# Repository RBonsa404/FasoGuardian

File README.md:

# FasoGuardian

Système intégré de sécurisation, d'identification et de géolocalisation des enfants au Burkina Faso :
un bracelet connecté, une plateforme serveur et des applications web pour les parents, les agents internes
et toute personne qui trouve un enfant. Projet du Collectif Dedsec (Ouagadougou).

## État d'avancement

Étape 1 « Socle » close le 8 octobre 2026 ; étape 2 en cours (module `identite` : inscription et sessions).
voir [docs/tracabilite.md](docs/tracabilite.md) pour le statut de chacune des 43 user stories.

## Organisation du dépôt

| Dossier | Contenu |
|---|---|
| `backend/` | Serveur Spring Boot 4 en monolithe modulaire : neuf modules métier et un socle technique |
| `frontend/` | Espace de travail Angular 22 : `site`, `parents`, `public-qr`, `console`, bibliothèques `ui` et `api` |
| `simulator/` | Simulateur de bracelets (MQTT en TLS mutuel) |
| `firmware/` | Logiciel embarqué du bracelet : noyau portable et ses essais (port matériel avec le prototype, ADR 0030) |
| `infra/` | Docker Compose, Mosquitto, Nginx, Prometheus, Grafana, Loki |
| `docs/` | ADR, protocoles d'essai, matrice de traçabilité |

## Prérequis

- JDK 21 (la variable `JAVA_HOME` doit pointer dessus), Node.js 24, Docker avec Compose, OpenSSL.
- Maven n'a pas besoin d'être installé : le dépôt fournit `backend/mvnw`.

## Démarrage

**Pour essayer l'application à la main, avec des comptes de démonstration : [docs/tester-en-local.md](docs/tester-en-local.md).**

Préparation, une seule fois : créer le fichier `.env` à partir de `.env.example`, y renseigner les mots de
passe, puis générer les certificats de développement.

```bash
cp .env.example .env
```

```bash
sh infra/generer-certificats-dev.sh
```

Démarrage de tout l'environnement (base, broker, serveur, proxy, observabilité) :

```bash
docker compose --env-file .env -f infra/docker-compose.yml up --build
```

| Service | Adresse |
|---|---|
| API par le proxy (certificat de développement auto-signé) | https://localhost:8443/api/v1/ |
| Broker MQTT (TLS mutuel) | ssl://localhost:8883 |
| Prometheus | http://localhost:9090 |
| Grafana | http://localhost:3000 |

Applications clientes en développement :

```bash
cd frontend && npm ci && npx ng serve parents --proxy-config proxy.dev.json
```

Le fichier `proxy.dev.json` relaie `/api` vers un serveur lancé en local sur le port 8080. Sous le profil
`dev`, les SMS de l'adaptateur bac à sable se lisent sur `GET /api/v1/dev/sms`.

Simulateur de bracelets :

```bash
cd simulator && ../backend/mvnw -f pom.xml package && java -jar target/fasoguardian-simulateur-0.1.0-SNAPSHOT.jar --certificats=../infra/certs --bracelets=FG-DEV-0001,FG-DEV-0002 --intervalle=PT10S --duree=PT1M --cle-plateforme=<clé publique de la plateforme>
```

## Tests

```bash
cd backend && ./mvnw verify
```

```bash
cd frontend && npm test && npm run build && npm run budgets -- parents
```

Les tests d'intégration du serveur démarrent PostgreSQL / PostGIS avec Testcontainers : Docker doit être lancé.

## Architecture

Client-serveur à trois niveaux : applications Angular servies en fichiers statiques, serveur Spring Boot
derrière Nginx, PostgreSQL / PostGIS. Les bracelets communiquent par MQTT en TLS avec authentification
mutuelle, avec repli par SMS signé. Le serveur est découpé en neuf modules (`identite`, `famille`,
`dispositifs`, `telemetrie`, `geolocalisation`, `alertes`, `notifications`, `abonnements`, `audit`) dont les
frontières sont vérifiées à chaque construction.

## Documentation

- Documents de conception FG-DOC-01 à FG-DOC-11 : diffusion restreinte, conservés hors du dépôt
- [Décisions d'architecture](docs/adr/README.md)
- [Matrice de traçabilité](docs/tracabilite.md)
- [Protocoles d'essai](docs/essais/README.md)
- [Guide de contribution](CONTRIBUTING.md)

## Données personnelles

Le projet traite des données d'identité, de santé et de géolocalisation de mineurs. Les données de
démonstration sont fictives. La mise en production avec des données réelles est subordonnée à l'analyse
d'impact (AIPD), à la désignation d'un délégué à la protection des données et aux formalités auprès de la CIL.

## Licence

[MIT](LICENSE) — © 2026 Collectif Dedsec.

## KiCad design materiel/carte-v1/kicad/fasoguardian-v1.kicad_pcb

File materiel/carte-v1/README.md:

# Carte électronique V1 du bracelet

Circuit imprimé de l'étape V1 « Premier circuit » de FG-DOC-08 (§ 12) : 6 couches, 1,2 mm, ENIG, 41 × 36 mm, assemblage
double face. Les décisions et les écarts au document de conception sont dans [CAHIER.md](CAHIER.md) et
[l'ADR 0042](../../docs/adr/0042-carte-v1-du-bracelet.md).

## Une seule source de vérité

Tout part de [conception/carte.py](conception/carte.py). Pour chaque composant, il décrit :
- son symbole et son empreinte ;
- sa valeur, sa référence fabricant et LCSC ;
- sa face d'assemblage ;
- la liaison de chacune de ses broches, par numéro contrôlé sur la fiche du fabricant.

Le schéma, le circuit imprimé et le dossier de fabrication sont générés à partir de ce fichier. On ne les retouche
pas à la main : on corrige `carte.py`, puis on rejoue la chaîne.

## Chaîne de réalisation et points de contrôle

| Étape | Commande | Contrôle |
|---|---|---|
| 1. Netlist | `python conception/verifier.py` | Règles du bracelet : broches du tableau 8 et fonctions alternatives, domaines 1,8 / 3,3 V, PWRKEY et RESET, adresses I²C, réservoir ≥ 300 µF, ≤ 100 µF sur SYS, découplage de chaque rail, hauteur en face inférieure |
| 2. Schéma | `python conception/generer_schema.py` puis `kicad-cli sch erc` | ERC sans erreur ni avertissement, broches typées d'après les fiches (`typer_broches.py`) |
| 3. Placement | `KICAD_PY conception/generer_carte.py` | DRC avec parité schéma ↔ carte ; chemin du courant fort du modem pré-routé et verrouillé |
| 4. Routage | `KICAD_PY conception/relier_plans.py avant`, `KICAD_PY conception/router.py 60` (Freerouting), `KICAD_PY conception/relier_plans.py`, `KICAD_PY conception/finir.py 14` (puis `finir.py fenetre 1.0` si un quartier reste saturé), `KICAD_PY conception/elargir.py` | DRC sans erreur ni avertissement, aucune liaison manquante ; `KICAD_PY conception/controler_carte.py` : lignes RF ≤ 20 mm et sans via, chemin du modem ≤ 30 mΩ de cuivre (`resistance.py`), rail 1V8 ≥ 0,25 mm, plan VBAT d'un seul tenant ; revue `KICAD_PY conception/auditer.py` (découplage au pied des broches, masse sous les lignes RF et coutures, îlots des plans, vias des pastilles thermiques, distance au bord) |
| 5. Fabrication | `python outils/rotations_jlc.py` (après tout changement d'empreinte), `KICAD_PY conception/modeles_3d.py`, puis `python conception/fabriquer.py` | Empreintes identiques à celles de LCSC en orientation et en centre (sinon `fabriquer.py` refuse le placement) ; modèles 3D recopiés de la bibliothèque, hauteur de la face inférieure ≤ 1,35 mm d'après les fiches des fabricants ; Gerber, perçage, netlist, nomenclature (une ligne par référence LCSC) et placement à la convention JLCPCB (rotation de la face inférieure : 180° − angle KiCad), PDF, STEP, rendus ; options de commande dans `fabrication/COMMANDE.md` |
| 6. Commande | `python outils/stock_jlc.py 5` | Stock et coût des pièces pour 5 cartes |
| 7. Guide | `KICAD_PY guide/plans.py`, puis `node guide/imprimer.mjs` | Plans de câblage et de mesure, guide PDF de commande et de mise en service |

`KICAD_PY` est l'interpréteur Python de KiCad :
`C:\Users\rachi\AppData\Local\Programs\KiCad\10.0\bin\python.exe`.
Outils utilisés :
- KiCad 10.0.6 ;
- Freerouting 2.5.0 (Java 25, appelé par son chemin ; le projet garde le JDK 21) ;
- `easyeda2kicad` pour importer les pièces LCSC dans `bibliotheque/`. Chaque pièce importée est contrôlée contre la
  fiche de son fabricant : l'empreinte du module A7670E l'a été plot par plot contre la table SIMCom.

Deux revues indépendantes ont été menées, l'une sur le cahier, l'autre sur le schéma. Leurs conclusions sont reprises
dans `CAHIER.md` et dans l'ADR 0042.

## Contenu

- `conception/` : netlist de référence, générateurs, contrôles.
- `bibliotheque/` : symboles, empreintes et modèles 3D des pièces LCSC.
- `kicad/` : projet KiCad généré (schéma, carte, rapports ERC et DRC).
- `fabrication/` : dossier à envoyer au façonnier.
- `guide/` : guide de commande et de mise en service (`guide-commande-et-mise-en-service.pdf`) et ses sources.
- `outils/` : recherche des références chez JLCPCB, stock et coût, comparaison des empreintes avec LCSC, calcul
  d'impédance.

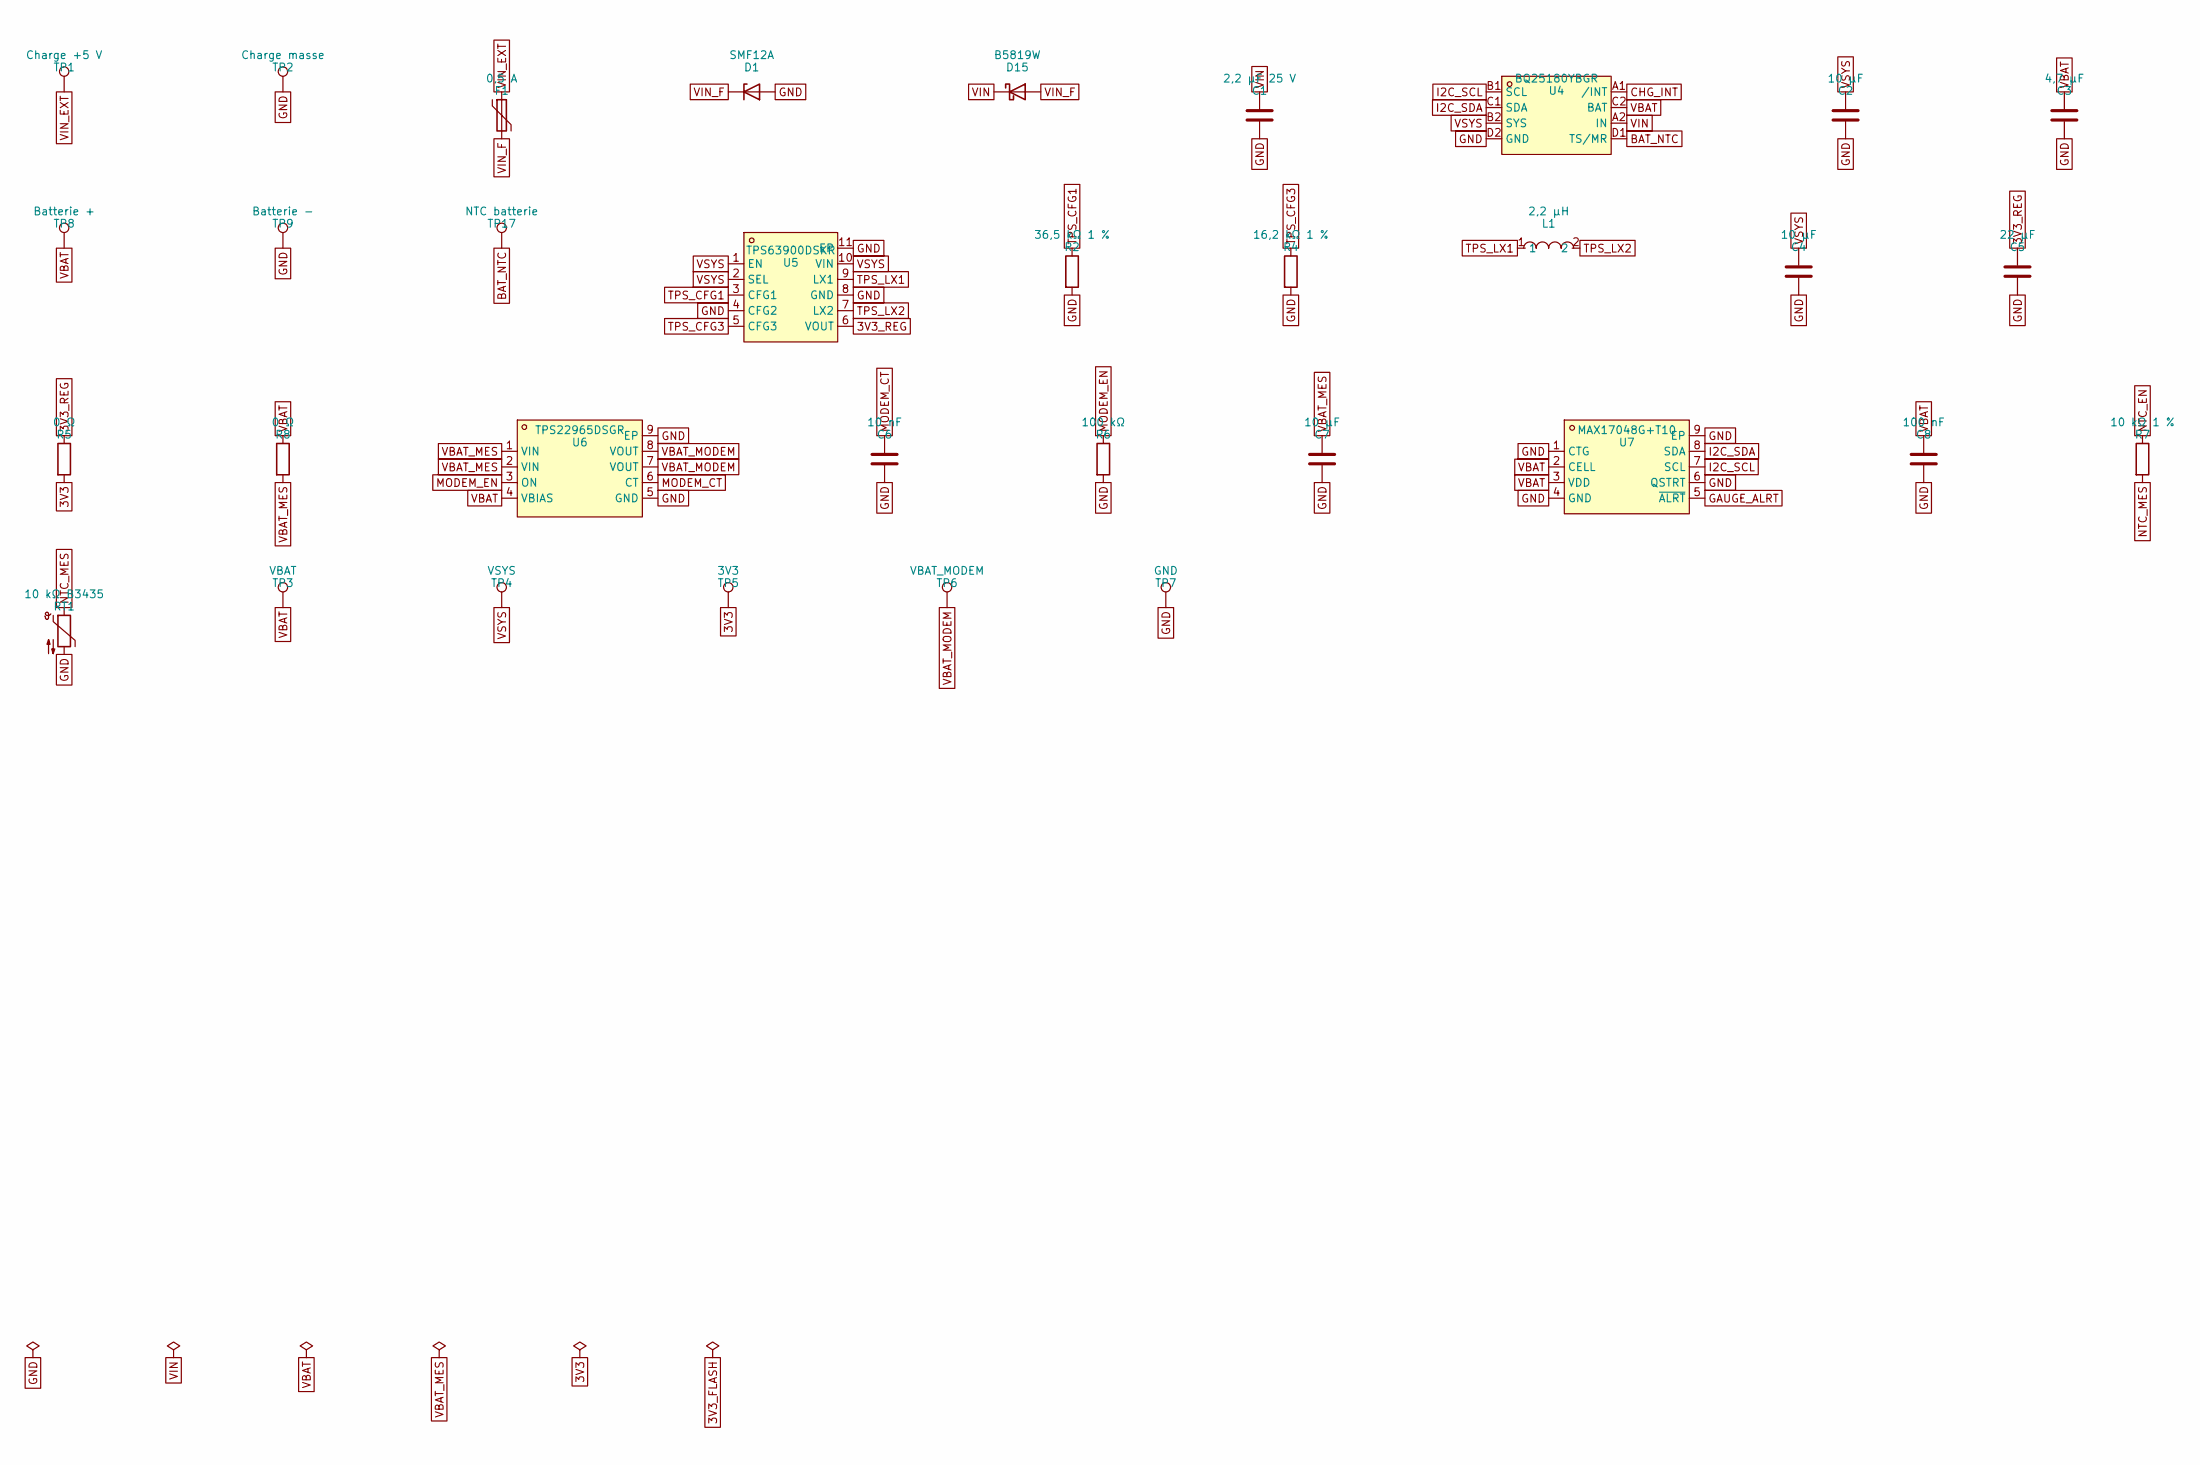
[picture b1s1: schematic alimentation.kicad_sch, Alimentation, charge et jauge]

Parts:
C1: 2,2 µF 25 V; C_0603_1608Metric; LCSC C57895
C2, C4, C7: 10 µF; C_0603_1608Metric; LCSC C19702
C3: 4,7 µF; C_0402_1005Metric; LCSC C23733
C5: 22 µF; C_0603_1608Metric; LCSC C59461
C6: 10 nF; C_0402_1005Metric; LCSC C15195
C8: 100 nF; C_0402_1005Metric; LCSC C1525
D1: SMF12A; D_SOD-123F; LCSC C123800
D15: B5819W; D_SOD-123; LCSC C8598
F1: 0,5 A; Fuse_0603_1608Metric; LCSC C207015
L1: 2,2 µH; L1008; LCSC C576403
R2: 36,5 kΩ 1 %; R_0402_1005Metric; LCSC C25887
R4: 16,2 kΩ 1 %; R_0402_1005Metric; LCSC C226806
R5: 0 Ω; R_0603_1608Metric; LCSC C21189
R6: 100 kΩ; R_0402_1005Metric; LCSC C25741
R7: 10 kΩ 1 %; R_0402_1005Metric; LCSC C25744
R8: 0 Ω; R_1206_3216Metric; LCSC C17888
RT1: 10 kΩ B3435; R_0402_1005Metric; LCSC C77131
TP1: Charge +5 V; TestPoint_Pad_2.5x2.5mm
TP2: Charge masse; TestPoint_Pad_2.5x2.5mm
TP3: VBAT; TestPoint_Pad_D1.0mm
TP4: VSYS; TestPoint_Pad_D1.0mm
TP5: 3V3; TestPoint_Pad_D1.0mm
TP6: VBAT_MODEM; TestPoint_Pad_D1.0mm
TP7: GND; TestPoint_Pad_D1.0mm
TP8: Batterie +; TestPoint_Pad_2.5x2.5mm
TP9: Batterie −; TestPoint_Pad_2.5x2.5mm
TP17: NTC batterie; TestPoint_Pad_1.5x1.5mm
U4: BQ25180YBGR; DSBGA-8_L1.6-W0.9-R2-C4-P0.40-BL; LCSC C3682423
U5: TPS63900DSKR; WSON-10_L2.5-W2.5-W0.50-TL-EP; LCSC C1518762
U6: TPS22965DSGR; UDFN-8_L2.0-W2.0-P0.50-TL-EP; LCSC C122837
U7: MAX17048G+T10; TDFN-8_L2.0-W2.0-P0.50-BL-EP1.2; LCSC C2682616

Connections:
3V3: R5.2, TP5.1; also elsewhere on the board
3V3_REG: C5.1, R5.1, U5.6 (VOUT)
BAT_NTC: TP17.1, U4.D1 (TS/MR)
CHG_INT: U4.A1 (/INT); also elsewhere on the board
GAUGE_ALRT: U7.5 (~ALRT); also elsewhere on the board
GND: C1.2, C2.2, C3.2, C4.2, C5.2, C6.2, C7.2, C8.2, D1.2 (A), R2.2, R4.2, R6.2, RT1.2, TP2.1, TP7.1, TP9.1, U4.D2 (GND), U5.4 (CFG2), U5.8 (GND), U5.11 (EP), U6.5 (GND), U6.9 (EP), U7.1 (CTG), U7.4 (GND), U7.6 (QSTRT), U7.9 (EP); also elsewhere on the board
I2C_SCL: U4.B1 (SCL), U7.7 (SCL); also elsewhere on the board
I2C_SDA: U4.C1 (SDA), U7.8 (SDA); also elsewhere on the board
MODEM_CT: C6.1, U6.6 (CT)
MODEM_EN: R6.1, U6.3 (ON); also elsewhere on the board
NTC_EN: R7.1; also elsewhere on the board
NTC_MES: R7.2, RT1.1; also elsewhere on the board
TPS_CFG1: R2.1, U5.3 (CFG1)
TPS_CFG3: R4.1, U5.5 (CFG3)
TPS_LX1: L1.1, U5.9 (LX1)
TPS_LX2: L1.2, U5.7 (LX2)
VBAT: C3.1, C8.1, R8.1, TP3.1, TP8.1, U4.C2 (BAT), U6.4 (VBIAS), U7.2 (CELL), U7.3 (VDD)
VBAT_MES: C7.1, R8.2, U6.1 (VIN), U6.2 (VIN)
VBAT_MODEM: TP6.1, U6.7 (VOUT), U6.8 (VOUT); also elsewhere on the board
VIN: C1.1, D15.1 (K), U4.A2 (IN)
VIN_EXT: F1.1, TP1.1
VIN_F: D1.1 (K), D15.2 (A), F1.2
VSYS: C2.1, C4.1, TP4.1, U4.B2 (SYS), U5.1 (EN), U5.2 (SEL), U5.10 (VIN); also elsewhere on the board

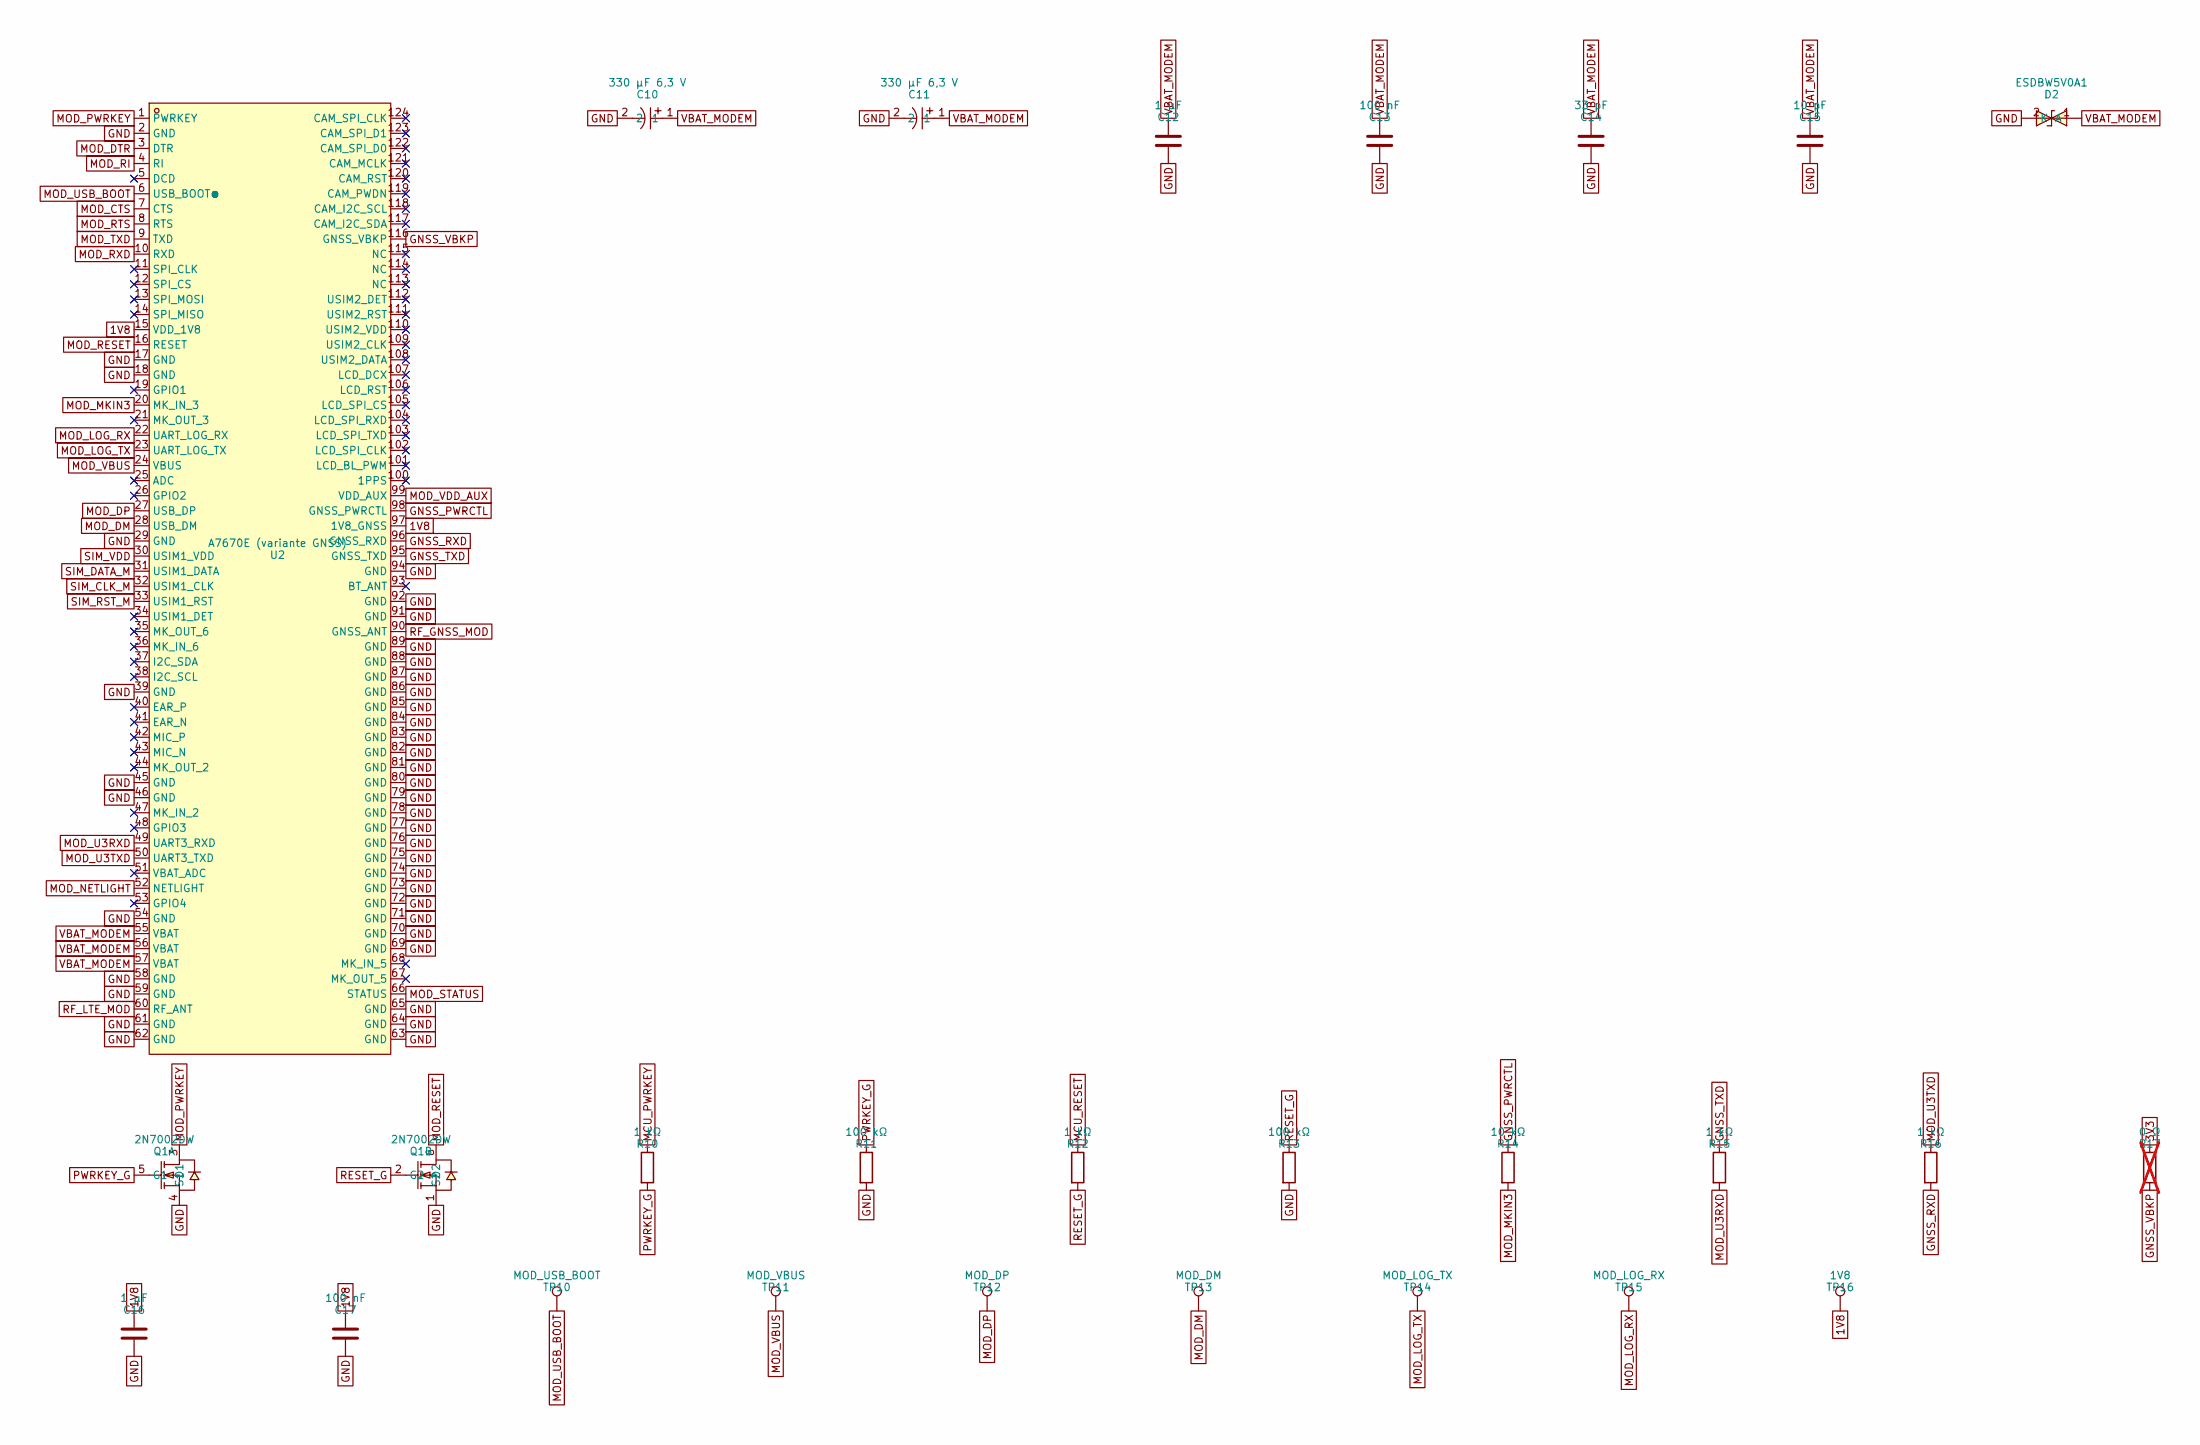
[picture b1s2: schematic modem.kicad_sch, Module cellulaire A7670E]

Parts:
C10, C11: 330 µF 6,3 V; CAP-SMD_L3.5-W2.8-R-RD; LCSC C696806
C12, C16: 1 µF; C_0402_1005Metric; LCSC C52923
C13, C17: 100 nF; C_0402_1005Metric; LCSC C1525
C14: 33 pF; C_0402_1005Metric; LCSC C1562
C15: 10 pF; C_0402_1005Metric; LCSC C32949
D2: ESDBW5V0A1; X1-DFN1006-2_L1.0-W0.6-P0.65-BI; LCSC C5173252
Q1: 2N7002DW; SOT-363_L2.0-W1.3-P0.65-LS2.1-TL; LCSC C83571
R10, R12, R15, R16: 1 kΩ; R_0402_1005Metric; LCSC C11702
R11, R13: 100 kΩ; R_0402_1005Metric; LCSC C25741
R14: 10 kΩ; R_0402_1005Metric; LCSC C25744
R17: 0 Ω; R_0402_1005Metric; LCSC C17168; not fitted
TP10: MOD_USB_BOOT; TestPoint_Pad_D1.0mm
TP11: MOD_VBUS; TestPoint_Pad_D1.0mm
TP12: MOD_DP; TestPoint_Pad_D1.0mm
TP13: MOD_DM; TestPoint_Pad_D1.0mm
TP14: MOD_LOG_TX; TestPoint_Pad_D1.0mm
TP15: MOD_LOG_RX; TestPoint_Pad_D1.0mm
TP16: 1V8; TestPoint_Pad_D1.0mm
U2: A7670E (variante GNSS); LGA-124_L24.0-W24.0-P1.0-A7670C-LASS; LCSC C7435296

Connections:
1V8: C16.1, C17.1, TP16.1, U2.15 (VDD_1V8), U2.97 (1V8_GNSS); also elsewhere on the board
3V3: R17.1; also elsewhere on the board
GND: C10.2, C11.2, C12.2, C13.2, C14.2, C15.2, C16.2, C17.2, D2.2 (A), Q1.1 (S2), Q1.4 (S1), R11.2, R13.2, U2.2 (GND), U2.17 (GND), U2.18 (GND), U2.29 (GND), U2.39 (GND), U2.45 (GND), U2.46 (GND), U2.54 (GND), U2.58 (GND), U2.59 (GND), U2.61 (GND), U2.62 (GND), U2.63 (GND), U2.64 (GND), U2.65 (GND), U2.69 (GND), U2.70 (GND), U2.71 (GND), U2.72 (GND), U2.73 (GND), U2.74 (GND), U2.75 (GND), U2.76 (GND), U2.77 (GND), U2.78 (GND), U2.79 (GND), U2.80 (GND), U2.81 (GND), U2.82 (GND), U2.83 (GND), U2.84 (GND), U2.85 (GND), U2.86 (GND), U2.87 (GND), U2.88 (GND), U2.89 (GND), U2.91 (GND), U2.92 (GND), U2.94 (GND); also elsewhere on the board
GNSS_PWRCTL: R14.1, U2.98 (GNSS_PWRCTL)
GNSS_RXD: R16.2, U2.96 (GNSS_RXD)
GNSS_TXD: R15.1, U2.95 (GNSS_TXD)
GNSS_VBKP: R17.2, U2.116 (GNSS_VBKP)
MCU_PWRKEY: R10.1; also elsewhere on the board
MCU_RESET: R12.1; also elsewhere on the board
MOD_CTS: U2.7 (CTS); also elsewhere on the board
MOD_DM: TP13.1, U2.28 (USB_DM)
MOD_DP: TP12.1, U2.27 (USB_DP)
MOD_DTR: U2.3 (DTR); also elsewhere on the board
MOD_LOG_RX: TP15.1, U2.22 (UART_LOG_RX)
MOD_LOG_TX: TP14.1, U2.23 (UART_LOG_TX)
MOD_MKIN3: R14.2, U2.20 (MK_IN_3)
MOD_NETLIGHT: U2.52 (NETLIGHT); also elsewhere on the board
MOD_PWRKEY: Q1.3 (D1), U2.1 (PWRKEY)
MOD_RESET: Q1.6 (D2), U2.16 (RESET)
MOD_RI: U2.4 (RI); also elsewhere on the board
MOD_RTS: U2.8 (RTS); also elsewhere on the board
MOD_RXD: U2.10 (RXD); also elsewhere on the board
MOD_STATUS: U2.66 (STATUS); also elsewhere on the board
MOD_TXD: U2.9 (TXD); also elsewhere on the board
MOD_U3RXD: R15.2, U2.49 (UART3_RXD)
MOD_U3TXD: R16.1, U2.50 (UART3_TXD)
MOD_USB_BOOT: TP10.1, U2.6 (USB_BOOT●)
MOD_VBUS: TP11.1, U2.24 (VBUS)
MOD_VDD_AUX: U2.99 (VDD_AUX); also elsewhere on the board
PWRKEY_G: Q1.5 (G1), R10.2, R11.1
RESET_G: Q1.2 (G2), R12.2, R13.1
RF_GNSS_MOD: U2.90 (GNSS_ANT); also elsewhere on the board
RF_LTE_MOD: U2.60 (RF_ANT); also elsewhere on the board
SIM_CLK_M: U2.32 (USIM1_CLK); also elsewhere on the board
SIM_DATA_M: U2.31 (USIM1_DATA); also elsewhere on the board
SIM_RST_M: U2.33 (USIM1_RST); also elsewhere on the board
SIM_VDD: U2.30 (USIM1_VDD); also elsewhere on the board
VBAT_MODEM: C10.1, C11.1, C12.1, C13.1, C14.1, C15.1, D2.1 (K), U2.55 (VBAT), U2.56 (VBAT), U2.57 (VBAT); also elsewhere on the board

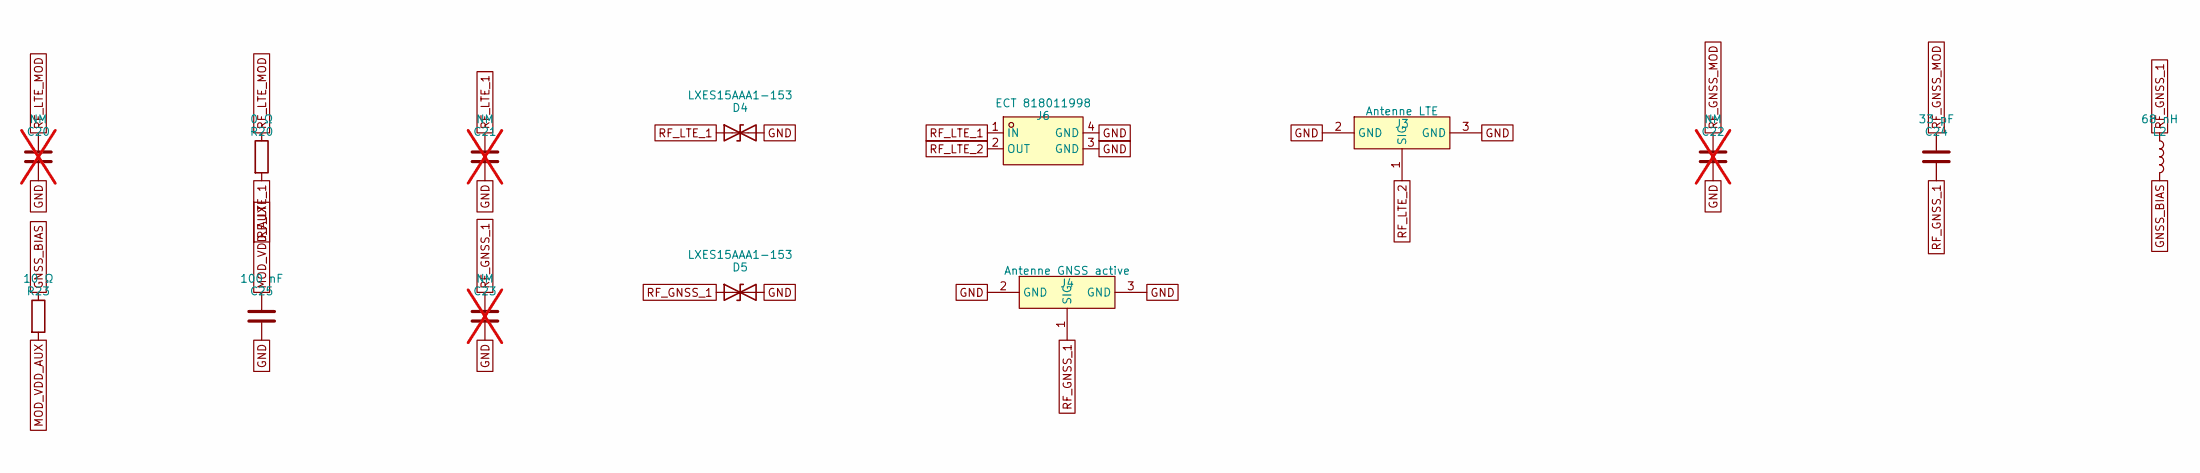
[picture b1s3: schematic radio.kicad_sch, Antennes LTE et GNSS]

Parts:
C20, C21, C22, C23: NM; C_0402_1005Metric; not fitted
C24: 33 pF; C_0402_1005Metric; LCSC C1562
C25: 100 nF; C_0402_1005Metric; LCSC C1525
D4, D5: LXES15AAA1-153; D_0402_1005Metric; LCSC C5210978
J3: Antenne LTE; RF-SMD_FRF05002-JSS103M; LCSC C88374
J4: Antenne GNSS active; RF-SMD_FRF05002-JSS103M; LCSC C88374
J6: ECT 818011998; IPEX-SMD_ECT818011998; LCSC C437250
L2: 68 nH; L_0402_1005Metric; LCSC C108965
R20: 0 Ω; R_0402_1005Metric; LCSC C17168
R23: 10 Ω; R_0402_1005Metric; LCSC C25077

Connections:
GND: C20.2, C21.2, C22.2, C23.2, C25.2, D4.2 (A2), D5.2 (A2), J3.2 (GND), J3.3 (GND), J4.2 (GND), J4.3 (GND), J6.3 (GND), J6.4 (GND); also elsewhere on the board
GNSS_BIAS: L2.2, R23.1
MOD_VDD_AUX: C25.1, R23.2; also elsewhere on the board
RF_GNSS_1: C23.1, C24.2, D5.1 (A1), J4.1 (SIG), L2.1
RF_GNSS_MOD: C22.1, C24.1; also elsewhere on the board
RF_LTE_1: C21.1, D4.1 (A1), J6.1 (IN), R20.2
RF_LTE_2: J3.1 (SIG), J6.2 (OUT)
RF_LTE_MOD: C20.1, R20.1; also elsewhere on the board

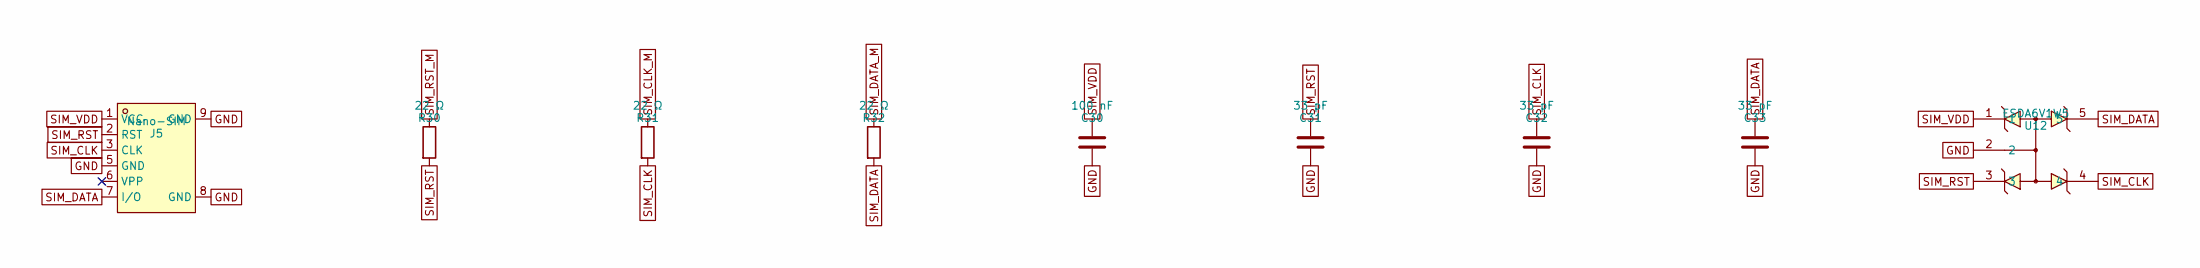
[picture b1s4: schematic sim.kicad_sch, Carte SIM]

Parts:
C30: 100 nF; C_0402_1005Metric; LCSC C1525
C31, C32, C33: 33 pF; C_0402_1005Metric; LCSC C1562
J5: Nano-SIM; SIM-SMD_NANO-SIM-TL6P-H1.35; LCSC C7529385
R30, R31, R32: 22 Ω; R_0402_1005Metric; LCSC C25092
U12: ESDA6V1W5; SC-70-5_L2.1-W1.3-P0.65-LS2.1-BR; LCSC C48677

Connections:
GND: C30.2, C31.2, C32.2, C33.2, J5.5 (GND), J5.8 (GND), J5.9 (GND), U12.2; also elsewhere on the board
SIM_CLK: C32.1, J5.3 (CLK), R31.2, U12.4
SIM_CLK_M: R31.1; also elsewhere on the board
SIM_DATA: C33.1, J5.7 (I/O), R32.2, U12.5
SIM_DATA_M: R32.1; also elsewhere on the board
SIM_RST: C31.1, J5.2 (RST), R30.2, U12.3
SIM_RST_M: R30.1; also elsewhere on the board
SIM_VDD: C30.1, J5.1 (VCC), U12.1; also elsewhere on the board

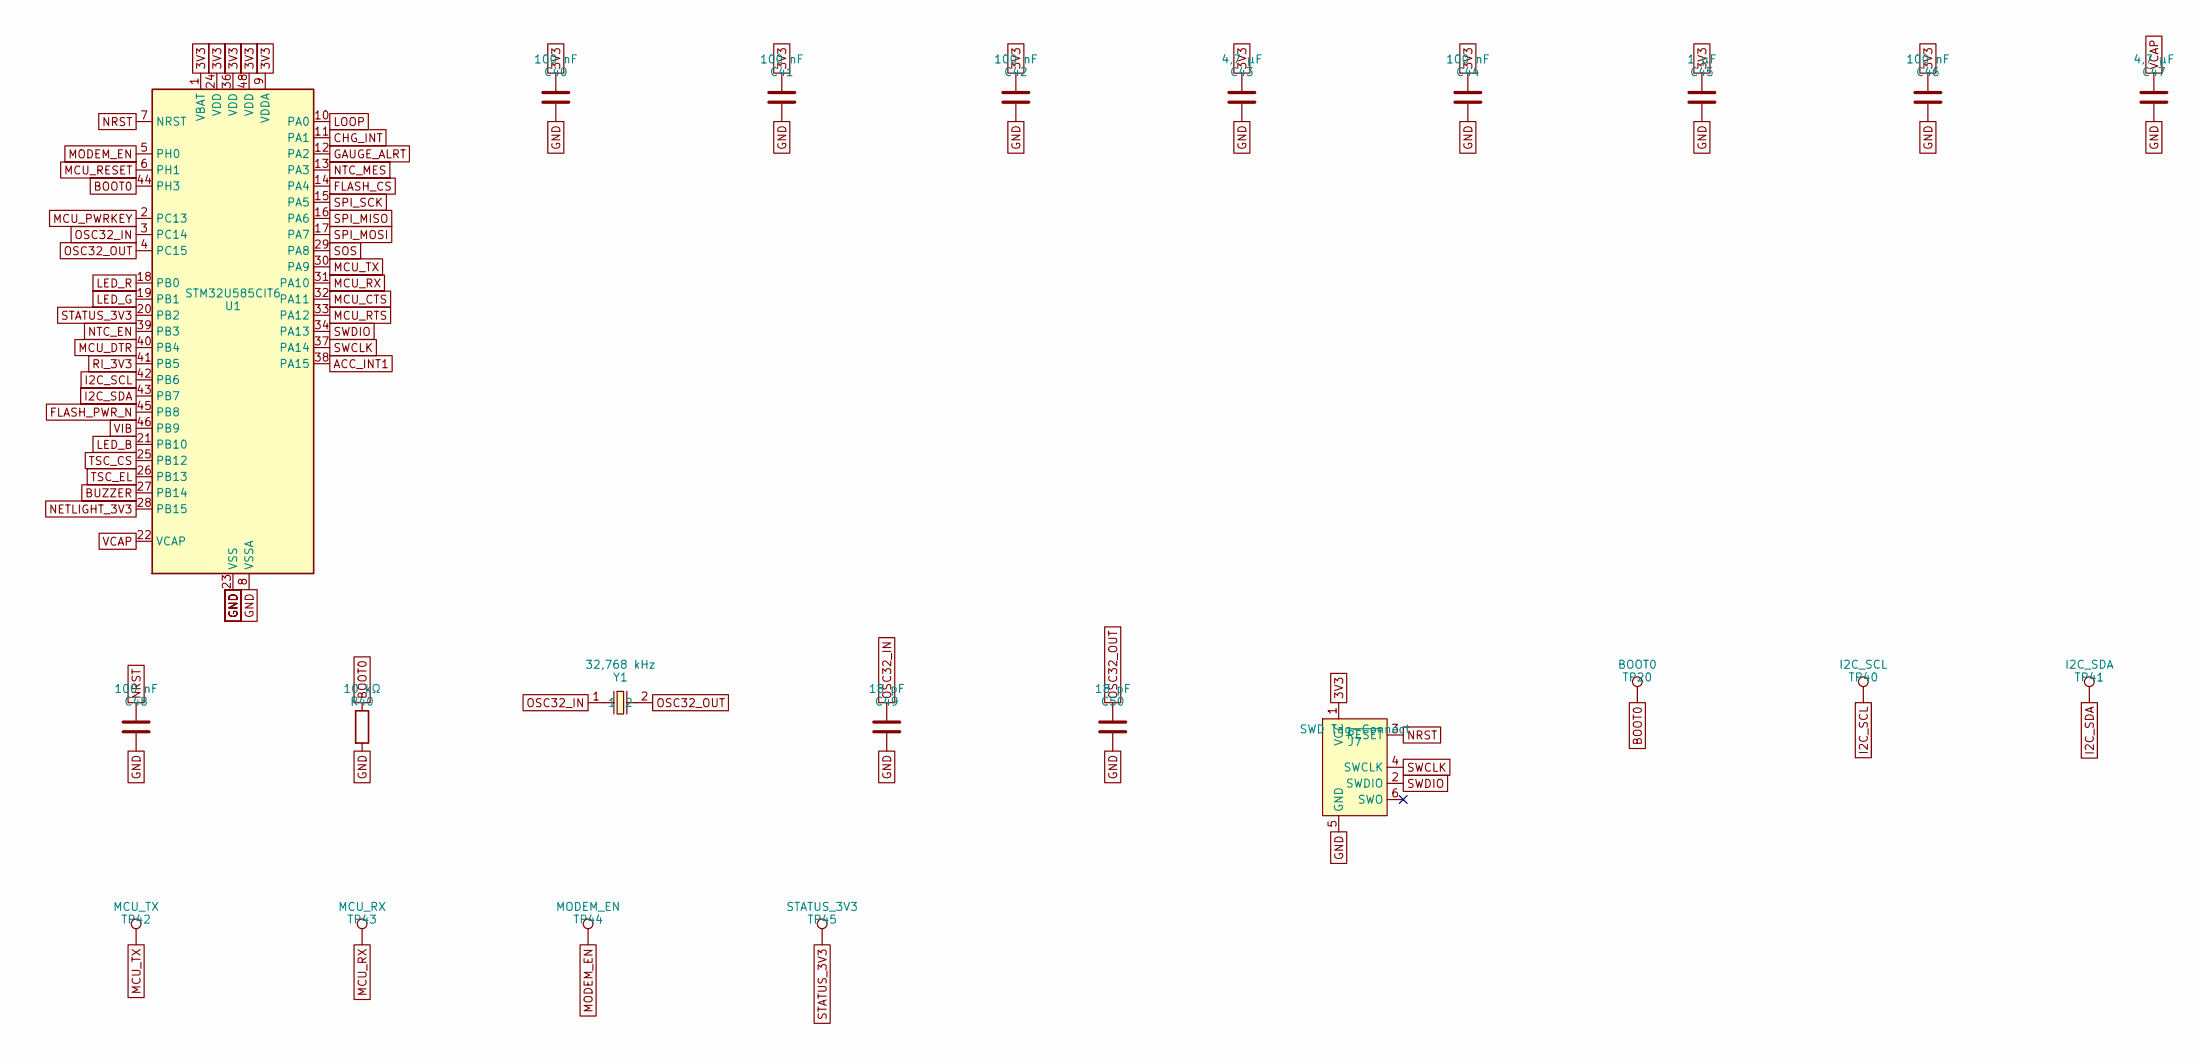
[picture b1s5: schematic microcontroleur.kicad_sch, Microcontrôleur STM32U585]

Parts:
C40, C41, C42, C44, C46, C48: 100 nF; C_0402_1005Metric; LCSC C1525
C43, C47: 4,7 µF; C_0402_1005Metric; LCSC C23733
C45: 1 µF; C_0402_1005Metric; LCSC C52923
C49, C50: 18 pF; C_0402_1005Metric; LCSC C1549
J7: SWD Tag-Connect; Tag-Connect_TC2030-IDC-NL_2x03_P1.27mm_Vertical
R40: 10 kΩ; R_0402_1005Metric; LCSC C25744
TP20: BOOT0; TestPoint_Pad_D1.0mm
TP40: I2C_SCL; TestPoint_Pad_D1.0mm
TP41: I2C_SDA; TestPoint_Pad_D1.0mm
TP42: MCU_TX; TestPoint_Pad_D1.0mm
TP43: MCU_RX; TestPoint_Pad_D1.0mm
TP44: MODEM_EN; TestPoint_Pad_D1.0mm
TP45: STATUS_3V3; TestPoint_Pad_D1.0mm
U1: STM32U585CIT6; LQFP-48_7x7mm_P0.5mm; LCSC C5271027
Y1: 32,768 kHz; CRYSTAL-SMD_L3.2-W1.5-FC-135R32.7680KF-A3; LCSC C20340322

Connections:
3V3: C40.1, C41.1, C42.1, C43.1, C44.1, C45.1, C46.1, J7.1 (VCC), U1.1 (VBAT), U1.9 (VDDA), U1.24 (VDD), U1.36 (VDD), U1.48 (VDD); also elsewhere on the board
ACC_INT1: U1.38 (PA15); also elsewhere on the board
BOOT0: R40.1, TP20.1, U1.44 (PH3)
BUZZER: U1.27 (PB14); also elsewhere on the board
CHG_INT: U1.11 (PA1); also elsewhere on the board
FLASH_CS: U1.14 (PA4); also elsewhere on the board
FLASH_PWR_N: U1.45 (PB8); also elsewhere on the board
GAUGE_ALRT: U1.12 (PA2); also elsewhere on the board
GND: C40.2, C41.2, C42.2, C43.2, C44.2, C45.2, C46.2, C47.2, C48.2, C49.2, C50.2, J7.5 (GND), R40.2, U1.8 (VSSA), U1.23 (VSS), U1.35 (VSS), U1.47 (VSS); also elsewhere on the board
I2C_SCL: TP40.1, U1.42 (PB6); also elsewhere on the board
I2C_SDA: TP41.1, U1.43 (PB7); also elsewhere on the board
LED_B: U1.21 (PB10); also elsewhere on the board
LED_G: U1.19 (PB1); also elsewhere on the board
LED_R: U1.18 (PB0); also elsewhere on the board
LOOP: U1.10 (PA0); also elsewhere on the board
MCU_CTS: U1.32 (PA11); also elsewhere on the board
MCU_DTR: U1.40 (PB4); also elsewhere on the board
MCU_PWRKEY: U1.2 (PC13); also elsewhere on the board
MCU_RESET: U1.6 (PH1); also elsewhere on the board
MCU_RTS: U1.33 (PA12); also elsewhere on the board
MCU_RX: TP43.1, U1.31 (PA10); also elsewhere on the board
MCU_TX: TP42.1, U1.30 (PA9); also elsewhere on the board
MODEM_EN: TP44.1, U1.5 (PH0); also elsewhere on the board
NETLIGHT_3V3: U1.28 (PB15); also elsewhere on the board
NRST: C48.1, J7.3 (~RESET), U1.7 (NRST)
NTC_EN: U1.39 (PB3); also elsewhere on the board
NTC_MES: U1.13 (PA3); also elsewhere on the board
OSC32_IN: C49.1, U1.3 (PC14), Y1.1
OSC32_OUT: C50.1, U1.4 (PC15), Y1.2
RI_3V3: U1.41 (PB5); also elsewhere on the board
SOS: U1.29 (PA8); also elsewhere on the board
SPI_MISO: U1.16 (PA6); also elsewhere on the board
SPI_MOSI: U1.17 (PA7); also elsewhere on the board
SPI_SCK: U1.15 (PA5); also elsewhere on the board
STATUS_3V3: TP45.1, U1.20 (PB2); also elsewhere on the board
SWCLK: J7.4 (SWCLK), U1.37 (PA14)
SWDIO: J7.2 (SWDIO), U1.34 (PA13)
TSC_CS: U1.25 (PB12); also elsewhere on the board
TSC_EL: U1.26 (PB13); also elsewhere on the board
VCAP: C47.1, U1.22 (VCAP)
VIB: U1.46 (PB9); also elsewhere on the board

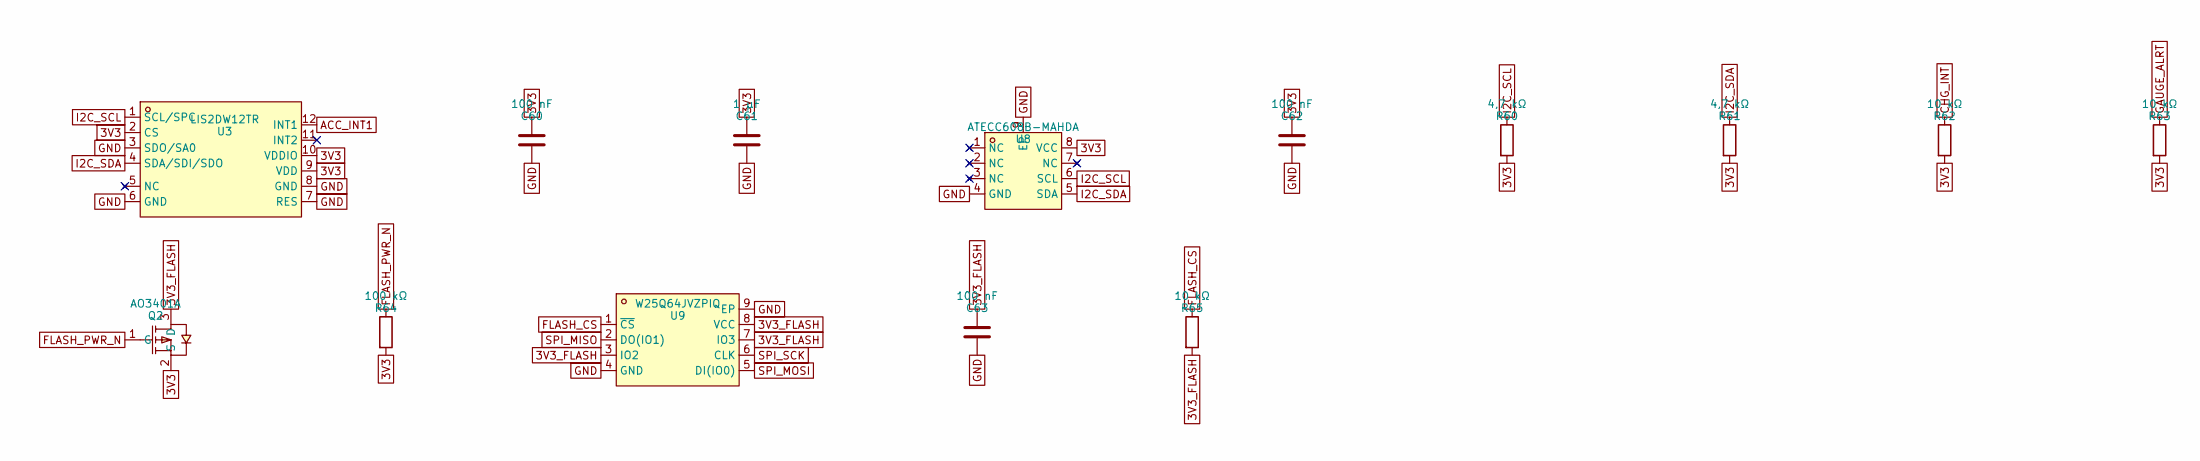
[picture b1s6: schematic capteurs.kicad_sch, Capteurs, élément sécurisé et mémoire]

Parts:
C60, C62, C63: 100 nF; C_0402_1005Metric; LCSC C1525
C61: 1 µF; C_0402_1005Metric; LCSC C52923
Q2: AO3401A; SOT-23_L2.9-W1.3-P1.90-LS2.4-BR; LCSC C15127
R60, R61: 4,7 kΩ; R_0402_1005Metric; LCSC C25900
R62, R63, R65: 10 kΩ; R_0402_1005Metric; LCSC C25744
R64: 100 kΩ; R_0402_1005Metric; LCSC C25741
U3: LIS2DW12TR; LGA-12_L2.0-W2.0-P0.50-BL; LCSC C189624
U8: ATECC608B-MAHDA; UDFN-8_L3.0-W2.0-P0.50-TL; LCSC C1518773
U9: W25Q64JVZPIQ; WSON-8_L6.0-W5.0-P1.27-BL-EP; LCSC C2940197

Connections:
3V3: C60.1, C61.1, C62.1, Q2.2 (S), R60.2, R61.2, R62.2, R63.2, R64.2, U3.2 (CS), U3.9 (VDD), U3.10 (VDDIO), U8.8 (VCC); also elsewhere on the board
3V3_FLASH: C63.1, Q2.3 (D), R65.2, U9.3 (IO2), U9.7 (IO3), U9.8 (VCC)
ACC_INT1: U3.12 (INT1); also elsewhere on the board
CHG_INT: R62.1; also elsewhere on the board
FLASH_CS: R65.1, U9.1 (~CS); also elsewhere on the board
FLASH_PWR_N: Q2.1 (G), R64.1; also elsewhere on the board
GAUGE_ALRT: R63.1; also elsewhere on the board
GND: C60.2, C61.2, C62.2, C63.2, U3.3 (SDO/SA0), U3.6 (GND), U3.7 (RES), U3.8 (GND), U8.4 (GND), U8.9 (EP), U9.4 (GND), U9.9 (EP); also elsewhere on the board
I2C_SCL: R60.1, U3.1 (SCL/SPC), U8.6 (SCL); also elsewhere on the board
I2C_SDA: R61.1, U3.4 (SDA/SDI/SDO), U8.5 (SDA); also elsewhere on the board
SPI_MISO: U9.2 (DO(IO1)); also elsewhere on the board
SPI_MOSI: U9.5 (DI(IO0)); also elsewhere on the board
SPI_SCK: U9.6 (CLK); also elsewhere on the board

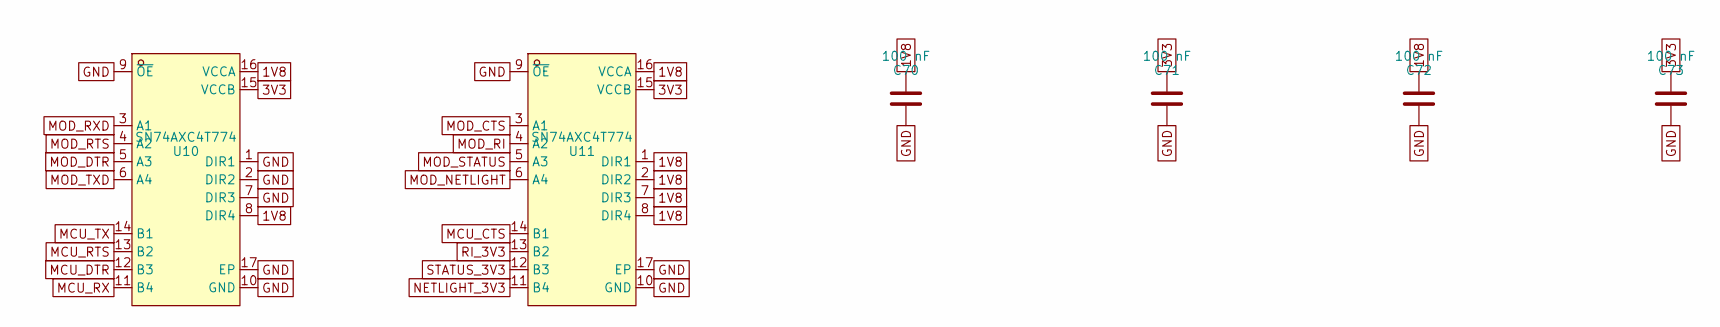
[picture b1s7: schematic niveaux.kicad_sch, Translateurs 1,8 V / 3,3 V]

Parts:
C70, C71, C72, C73: 100 nF; C_0402_1005Metric; LCSC C1525
U10, U11: SN74AXC4T774; DHVQFN-16_L3.5-W2.5-P0.50-BL-EP; LCSC C2862903

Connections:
1V8: C70.1, C72.1, U10.8 (DIR4), U10.16 (VCCA), U11.1 (DIR1), U11.2 (DIR2), U11.7 (DIR3), U11.8 (DIR4), U11.16 (VCCA); also elsewhere on the board
3V3: C71.1, C73.1, U10.15 (VCCB), U11.15 (VCCB); also elsewhere on the board
GND: C70.2, C71.2, C72.2, C73.2, U10.1 (DIR1), U10.2 (DIR2), U10.7 (DIR3), U10.9 (~OE), U10.10 (GND), U10.17 (EP), U11.9 (~OE), U11.10 (GND), U11.17 (EP); also elsewhere on the board
MCU_CTS: U11.14 (B1); also elsewhere on the board
MCU_DTR: U10.12 (B3); also elsewhere on the board
MCU_RTS: U10.13 (B2); also elsewhere on the board
MCU_RX: U10.11 (B4); also elsewhere on the board
MCU_TX: U10.14 (B1); also elsewhere on the board
MOD_CTS: U11.3 (A1); also elsewhere on the board
MOD_DTR: U10.5 (A3); also elsewhere on the board
MOD_NETLIGHT: U11.6 (A4); also elsewhere on the board
MOD_RI: U11.4 (A2); also elsewhere on the board
MOD_RTS: U10.4 (A2); also elsewhere on the board
MOD_RXD: U10.3 (A1); also elsewhere on the board
MOD_STATUS: U11.5 (A3); also elsewhere on the board
MOD_TXD: U10.6 (A4); also elsewhere on the board
NETLIGHT_3V3: U11.11 (B4); also elsewhere on the board
RI_3V3: U11.13 (B2); also elsewhere on the board
STATUS_3V3: U11.12 (B3); also elsewhere on the board
